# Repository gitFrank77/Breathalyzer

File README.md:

# Breathalyzer
CPU : attiny85-AU

Complete :  (Fan component added ||discrete output || : humidity control during ' dose step ').

TODO :  -build calibration unit on Schematic and PCB
        -test MiCS VOC sensor on analog input + enable pin mode
        -create header
        -make enclosure
        -test

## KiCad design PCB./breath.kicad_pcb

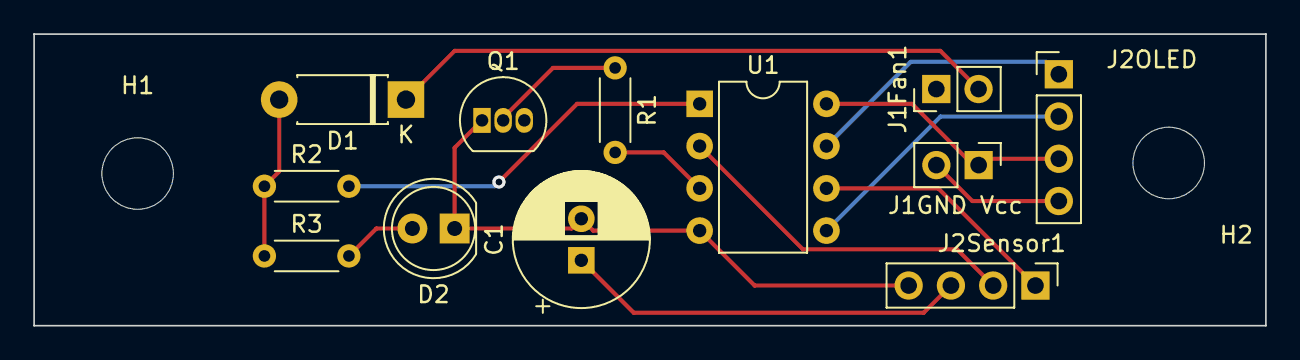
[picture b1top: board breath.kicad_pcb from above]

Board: 2 copper layers, 74.0 x 17.5 mm, 14 parts (0 on the bottom side), 12 nets.

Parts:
C1: 100; CP_Radial_D8.0mm_P2.50mm
D1: 1N53xxB; D_DO-41_SOD81_P7.62mm_Horizontal
D2: LED; LED_D5.0mm_Clear
H1, H2: MountingHole; MountingHole_4.3mm_M4
J1Fan1, J1GND Vcc: Conn_01x02_Female; PinHeader_1x02_P2.54mm_Vertical
J2OLED, J2Sensor1: Conn_01x04_Female; PinHeader_1x04_P2.54mm_Vertical
Q1: 2N3905; TO-92_Inline
R1: 10k; R_Axial_DIN0204_L3.6mm_D1.6mm_P5.08mm_Horizontal
R2: 10K; R_Axial_DIN0204_L3.6mm_D1.6mm_P5.08mm_Horizontal
R3: R330; R_Axial_DIN0204_L3.6mm_D1.6mm_P5.08mm_Horizontal
U1: ATtiny85-20P; DIP-8_W7.62mm

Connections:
/AI_OUT: J2Sensor1.2, U1.2 (XTAL1/PB3)
/Enable: J2Sensor1.1, U1.6 (PB1)
/Fan1: D1.1 (K), J1Fan1.2
/Fan2: J1Fan1.1, Q1.3 (C)
/SCL: J2OLED.1, U1.7 (PB2)
/SDA: J2OLED.2, U1.5 (AREF/PB0)
/Vcc: C1.1, D1.2 (A), J1GND Vcc.1, J2OLED.3, J2Sensor1.3, R2.1, R3.1, U1.8 (VCC)
GND: C1.2, D2.1 (K), J1GND Vcc.2, J2OLED.4, J2Sensor1.4, Q1.1 (E), U1.4 (GND)
unnamed: D2.2 (A), R3.2
unnamed: Q1.2 (B), R1.1
unnamed: R1.2, U1.3 (XTAL2/PB4)
unnamed: R2.2, U1.1 (~RESET/PB5)

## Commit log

2022-11-01 add new main with register config
2022-11-01 add ignore
